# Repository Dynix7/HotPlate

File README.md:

# HotPlate
This is a design for an solder reflow hotplate controlled by an RP2040.

# Why I Made It
I made this PCB since I plan to solder more components in the future. But I currently only have an solder iron which is too big for smaller SMD components, so I can use this to easily solder those smaller components.

# Picture

|Name                      |Purpose                  |Quantity|Total Cost (USD)|Link                                                     |Distributor|
|--------------------------|-------------------------|--------|----------------|---------------------------------------------------------|-----------|
|70mm round Polymide Heater|Heating Element          |1       |3.92            |https://www.aliexpress.us/item/2255801077213882.html?mp=1|Aliexpress |
|PCB Stencil               |For Manual PCB Assembly  |1       |7.11            |                                                         |JLCPCB     |
|PCB                       |PCB for Build            |5       |5.10            |                                                         |JLCPCB     |
|100n Capacitor            |Capacitor                |100     |0.23            |https://www.lcsc.com/product-detail/C6119867.html        |LCSC       |
|1uF Capacitor             |Capacitor                |50      |0.27            |https://www.lcsc.com/product-detail/C59782.html          |LCSC       |
|10uF Capacitor            |Capacitor                |50      |0.40            |https://www.lcsc.com/product-detail/C19702.html          |LCSC       |
|12pF Capacitor            |Crystal Load Capacitors  |100     |0.28            |https://www.lcsc.com/product-detail/C45359931.html       |LCSC       |
|10k Resistor              |Resistor                 |100     |0.10            |https://www.lcsc.com/product-detail/C2930027.html        |LCSC       |
|1k Resistor               |Resistor                 |100     |0.09            |https://www.lcsc.com/product-detail/C2907113.html        |LCSC       |
|5.1k Resistor             |Resistor                 |100     |0.10            |https://www.lcsc.com/product-detail/C2907114.html        |LCSC       |
|27 Resistor               |Resistor                 |100     |0.10            |https://www.lcsc.com/product-detail/C2907021.html        |LCSC       |
|2.7k Resistor             |Resistor                 |100     |0.15            |https://www.lcsc.com/product-detail/C13167.html          |LCSC       |
|10 Resistor               |Resistor                 |20      |0.04            |https://www.lcsc.com/product-detail/C22859.html          |LCSC       |
|49.9 Resistor             |Resistor                 |100     |0.11            |https://www.lcsc.com/product-detail/C2930110.html        |LCSC       |
|22.6k Resistor            |REsistor                 |100     |0.12            |https://www.lcsc.com/product-detail/C2999509.html        |LCSC       |
|LED                       |Indicator LEDs           |50      |0.40            |https://www.lcsc.com/product-detail/C2827254.html        |LCSC       |
|100Ohm Resistor           |Resistor                 |100     |0.10            |https://www.lcsc.com/product-detail/C2906981.html        |LCSC       |
|Push Button               |Reset, Boot, Menu Buttons|20      |0.34            |https://www.lcsc.com/product-detail/C18078070.html       |LCSC       |
|SX3B12.000F1210F30 Crystal|Clock for RP2040         |5       |0.36            |https://www.lcsc.com/product-detail/C2901650.html        |LCSC       |
|LUTE 2920L500/30GR Fuse   |Prevents Overheating     |5       |0.74            |https://www.lcsc.com/product-detail/C19078763.html       |LCSC       |
|L78L33ACUTR               |Voltage Regulator        |5       |0.49            |https://www.lcsc.com/product-detail/C22358668.html       |LCSC       |
|USBLC6-2SC6               |Power Protection         |5       |0.77            |https://www.lcsc.com/product-detail/C7519.html           |LCSC       |
|RP2040                    |Microcontroller          |1       |0.95            |https://www.lcsc.com/product-detail/C2040.html           |LCSC       |
|HUSB238 USB PD Chip       | USB Power Delivery      |1       |0.50            |https://www.lcsc.com/product-detail/C7471904.html        |LCSC       |
|W25Q32JVSSIQ Flash Chip   |Storage of Program       |5       |7.51            |https://www.lcsc.com/product-detail/C179173.html         |LCSC       |
|N-Channel MOSFET          |Power Control            |5       |0.58            |https://www.lcsc.com/product-detail/C2902884.html        |LCSC       |
|P-Channel MOSFET          |Control Power            |1       |0.34            |https://www.lcsc.com/product-detail/C5277951.html        |LCSC       |
|2 Pin Terminal Block      |To Power Heating Element |5       |0.42            |https://www.lcsc.com/product-detail/C695629.html         |LCSC       |
|USB-C Receptacle          |Power                    |5       |0.41            |https://www.lcsc.com/product-detail/C2988369.html        |LCSC       |
|NTC Thermistor 100kΩ      |Thermometer              |5       |1.28            |https://www.lcsc.com/product-detail/C5355638.html        |LCSC       |

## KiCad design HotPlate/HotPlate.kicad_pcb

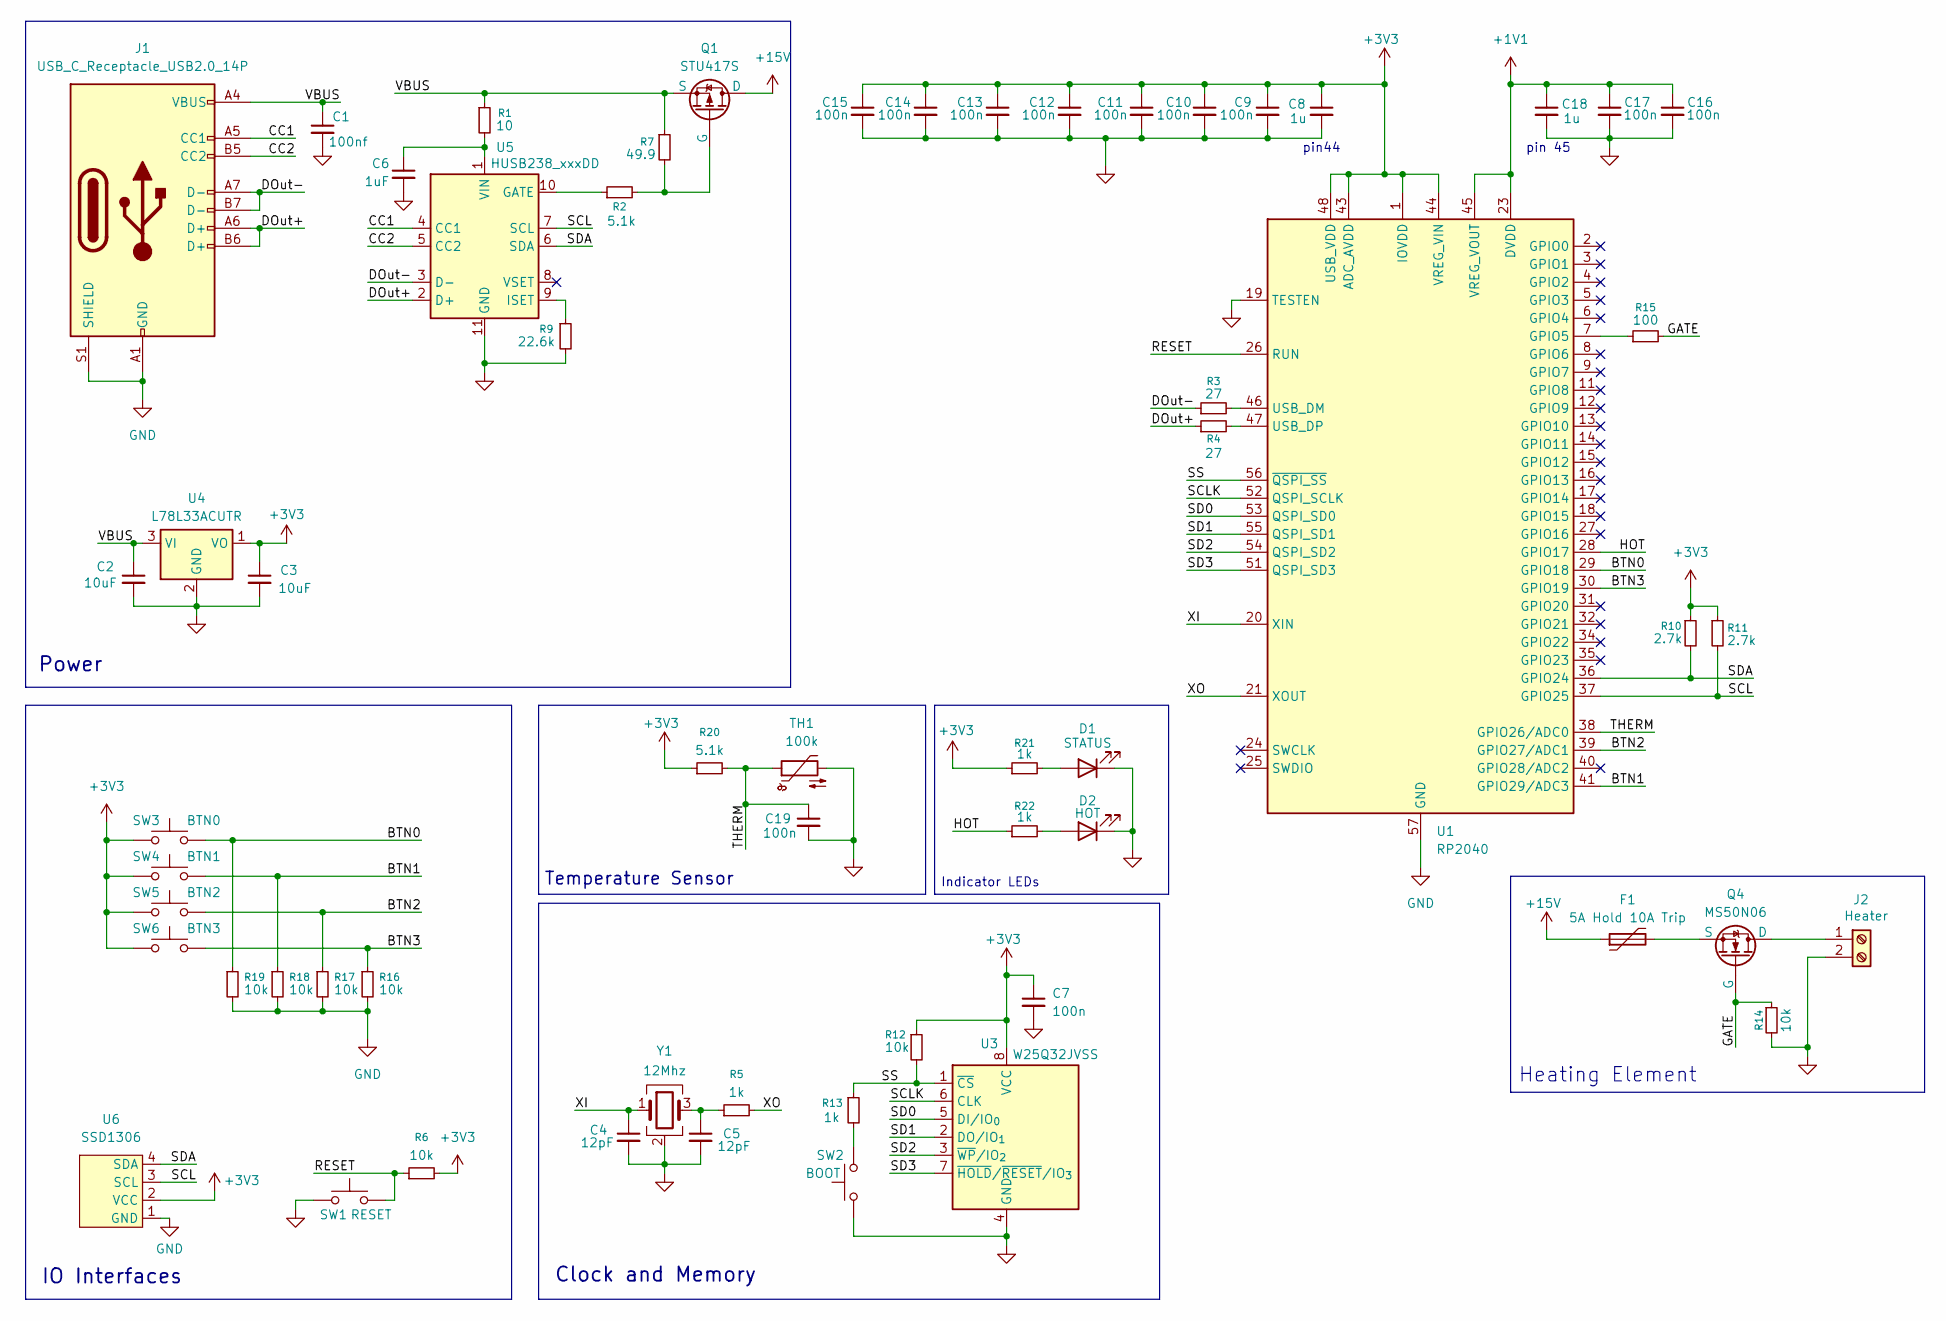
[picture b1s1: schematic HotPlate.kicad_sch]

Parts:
C1: 100nf; C_0603_1608Metric
C2, C3: 10uF; C_0603_1608Metric
C4, C5: 12pF; C_0603_1608Metric
C6: 1uF; C_0603_1608Metric
C7, C9, C10, C11, C12, C13, C14, C15, C16, C17, C19: 100n; C_0603_1608Metric
C8, C18: 1u; C_0603_1608Metric
D1: STATUS; D_1206_3216Metric
D2: HOT; D_1206_3216Metric
F1: 5A Hold 10A Trip; Fuse_2920_7451Metric
J1: USB_C_Receptacle_USB2.0_14P; USB_C_Receptacle_G-Switch_GT-USB-7010ASV
J2: Heater; TerminalBlock_Phoenix_PT-1,5-2-3.5-H_1x02_P3.50mm_Horizontal
Q1: STU417S; TO-252-2
Q4: MS50N06; TO-252-2
R1: 10; R_0603_1608Metric
R2, R20: 5.1k; R_0603_1608Metric
R3, R4: 27; R_0603_1608Metric
R5, R13, R21, R22: 1k; R_0603_1608Metric
R6, R12, R14, R16, R17, R18, R19: 10k; R_0603_1608Metric
R7: 49.9; R_0603_1608Metric
R9: 22.6k; R_0603_1608Metric
R10, R11: 2.7k; R_0603_1608Metric
R15: 100; R_0603_1608Metric
SW1: RESET; SW_SPST_PTS647_Sx38
SW2: BOOT; SW_SPST_PTS647_Sx38
SW3: BTN0; SW_SPST_PTS647_Sx38
SW4: BTN1; SW_SPST_PTS647_Sx38
SW5: BTN2; SW_SPST_PTS647_Sx38
SW6: BTN3; SW_SPST_PTS647_Sx38
TH1: 100k; R_Axial_DIN0204_L3.6mm_D1.6mm_P5.08mm_Horizontal
U1: RP2040; QFN-56-1EP_7x7mm_P0.4mm_EP3.2x3.2mm
U3: W25Q32JVSS; SOIC-8_5.3x5.3mm_P1.27mm
U4: L78L33ACUTR; SOT-89-3
U5: HUSB238_xxxDD; WDFN-10-1EP_3x3mm_P0.5mm_EP1.8x2.5mm
U6: SSD1306; PinHeader_1x04_P2.54mm_Vertical
Y1: 12Mhz; Oscillator_SMD_SeikoEpson_SG8002CE-4Pin_3.2x2.5mm

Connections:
+1V1: C16.1, C17.1, C18.1, U1.23 (DVDD), U1.45 (VREG_VOUT), U1.50 (DVDD)
+3V3: C3.1, C7.1, C8.1, C9.1, C10.1, C11.1, C12.1, C13.1, C14.1, C15.1, R6.2, R10.1, R11.1, R12.1, R20.1, R21.1, SW3.1, SW4.1, SW5.1, SW6.1, U1.1 (IOVDD), U1.10 (IOVDD), U1.22 (IOVDD), U1.33 (IOVDD), U1.42 (IOVDD), U1.43 (ADC_AVDD), U1.44 (VREG_VIN), U1.48 (USB_VDD), U1.49 (IOVDD), U3.8 (VCC), U4.1 (VO), U6.2 (VCC)
+15V: F1.1, Q1.2 (D)
/BTN0: R19.1, SW3.2, U1.29 (GPIO18)
/BTN1: R18.1, SW4.2, U1.41 (GPIO29/ADC3)
/BTN2: R17.1, SW5.2, U1.39 (GPIO27/ADC1)
/BTN3: R16.1, SW6.2, U1.30 (GPIO19)
/CC1: J1.A5 (CC1), U5.4 (CC1)
/CC2: J1.B5 (CC2), U5.5 (CC2)
/DOut+: J1.A6 (D+), J1.B6 (D+), R4.1, U5.2 (D+)
/DOut-: J1.A7 (D-), J1.B7 (D-), R3.1, U5.3 (D-)
/GATE: Q4.1 (G), R14.1, R15.2
/HOT: R22.1, U1.28 (GPIO17)
/RESET: R6.1, SW1.2, U1.26 (RUN)
/SCL: R11.2, U1.37 (GPIO25), U5.7 (SCL), U6.3 (SCL)
/SCLK: U1.52 (QSPI_SCLK), U3.6 (CLK)
/SD0: U1.53 (QSPI_SD0), U3.5 (DI/IO_{0})
/SD1: U1.55 (QSPI_SD1), U3.2 (DO/IO_{1})
/SD2: U1.54 (QSPI_SD2), U3.3 (~WP/IO_{2})
/SD3: U1.51 (QSPI_SD3), U3.7 (~HOLD/~RESET/IO_{3})
/SDA: R10.2, U1.36 (GPIO24), U5.6 (SDA), U6.4 (SDA)
/SS: R12.2, R13.1, U1.56 (~QSPI_SS), U3.1 (~CS)
/THERM: C19.1, R20.2, TH1.1, U1.38 (GPIO26/ADC0)
/VBUS: C1.1, C2.1, J1.A4 (VBUS), J1.A9 (VBUS), J1.B4 (VBUS), J1.B9 (VBUS), Q1.3 (S), R1.1, R7.1, U4.3 (VI)
/XI: C4.1, U1.20 (XIN), Y1.1
/XO: R5.2, U1.21 (XOUT)
GND: C1.2, C2.2, C3.2, C4.2, C5.2, C6.2, C7.2, C8.2, C9.2, C10.2, C11.2, C12.2, C13.2, C14.2, C15.2, C16.2, C17.2, C18.2, C19.2, D1.1 (K), D2.1 (K), J1.A1 (GND), J1.A12 (GND), J1.B1 (GND), J1.B12 (GND), J1.S1 (SHIELD), J2.2, R9.2, R14.2, R16.2, R17.2, R18.2, R19.2, SW1.1, SW2.1, TH1.2, U1.19 (TESTEN), U1.57 (GND), U3.4 (GND), U4.2 (GND), U5.11 (GND), U6.1 (GND), Y1.2 (G), Y1.4 (G)
unnamed: C5.1, R5.1, Y1.3
unnamed: D1.2 (A), R21.2
unnamed: D2.2 (A), R22.2
unnamed: J2.1, Q4.2 (D)
unnamed: Q1.1 (G), R2.2, R7.2
unnamed: F1.2, Q4.3 (S)
unnamed: R13.2, SW2.2
unnamed: R15.1, U1.7 (GPIO5)
unnamed: R3.2, U1.46 (USB_DM)
unnamed: R4.2, U1.47 (USB_DP)
unnamed: R2.1, U5.10 (GATE)
unnamed: R9.1, U5.9 (ISET)
unnamed: C6.1, R1.2, U5.1 (VIN)

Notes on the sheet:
Power
IO Interfaces
Heating Element
pin44
Temperature Sensor
Clock and Memory
Indicator LEDs
pin 45

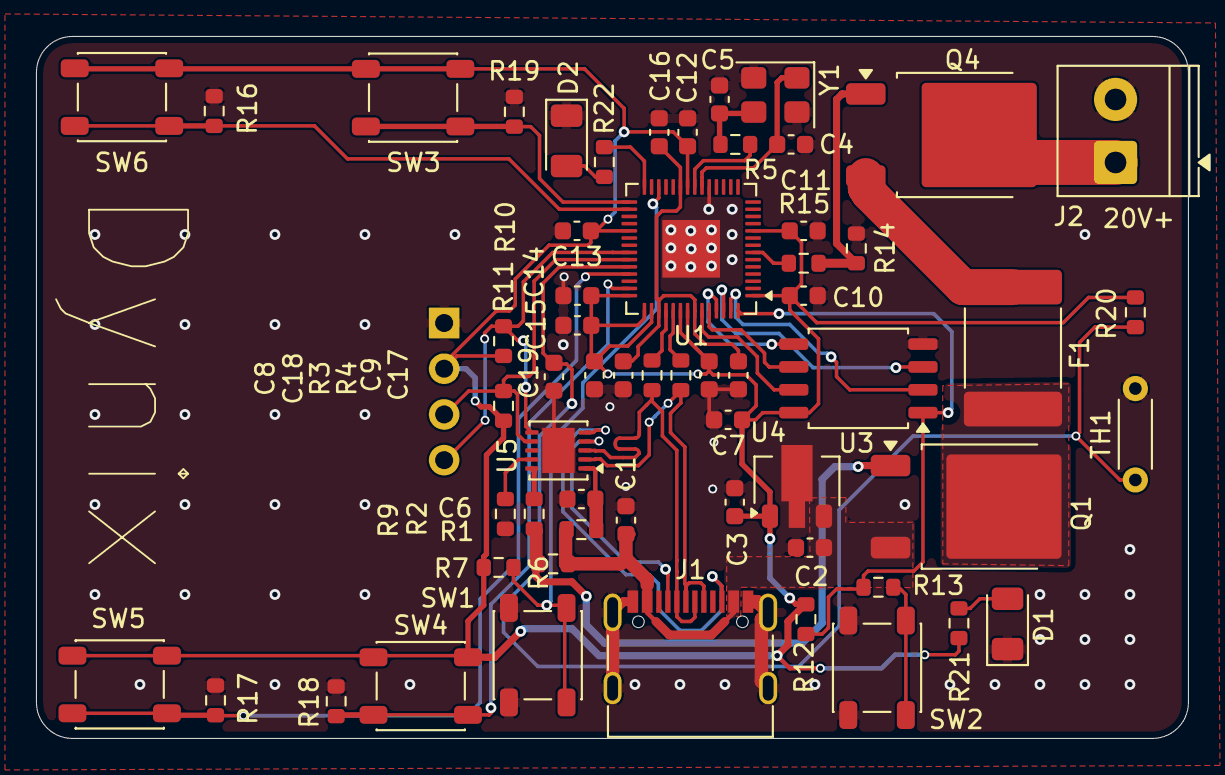
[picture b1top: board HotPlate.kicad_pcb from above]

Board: 2 copper layers, 64.0 x 39.0 mm, 60 parts (1 on the bottom side), 40 nets.

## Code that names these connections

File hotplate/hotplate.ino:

#include <Wire.h>
#include <Adafruit_SSD1306.h>
#include <Thermistor.h>
#include <NTC_Thermistor.h>

#include "thermistor.hpp"
#include "temperature.hpp"
#include "screen.hpp"
#include "helper.hpp"
#include "config.hpp"


NTC_Thermistor thermistor(THERM, REF_RESISTOR, NTC_RESISTANCE, NTC_REF_TEMP, B_VALUE, ANALOG_RES);
Adafruit_SSD1306 OLED_1306(SCREEN_WIDTH, SCREEN_HEIGHT, SCREEN_WIRE, OLED_RESET);

enum PLATESTATE currentState = STARTUP;

struct HEATINGPROFILE profile = {
    .targetTemps = {150.0, 220.0}, // Soak Temp, Reflow Temp-Celsius
    .targetTimes = {100, 60}, //Length of Soak, Length of Reflow-Seconds
    .targetRates = {2.5, 2.5, 3.5} // Start->Soak, Soak->Reflow, Reflow->End  -  Celsius/Second
}

HotPlateScreen SCREEN(&OLED_1306, &profile, &currentState);

void setup() {
    Serial.begin(115200);

    //I2C stuff
    Wire.begin();
    Wire.setSDA(SDA);
    Wire.setSCL(SCL);

    // Pinout Setup
    pinMode(BTN0, INPUT);
    pinMode(BTN1, INPUT);
    pinMode(BTN2, INPUT);
    pinMode(BTN3, INPUT);

    pinMode(GATE, OUTPUT);
    pinMode(HOT, OUTPUT); //LED

    pinMode(THERM, INPUT);

    SCREEN.initScreen();
}

void loop() {

  SCREEN.updateScreen();

}

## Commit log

2026-03-08 Initial USB and RP2040 Schematic
2026-03-09 Wire up power delivery, and memory
2026-03-10 Re-add buttons and add thermistor
2026-03-13 Wire Buttons, screen, thermistor, fuse
2026-03-14 Status LEDs
2026-03-15 Begin PCB placements and routing
2026-03-15 Finish routing
2026-03-19 Minor placement changes and ground vias
2026-03-21 Started Code and Added Name to PCB
2026-03-24 Minor code changes
2026-03-28 code for screen
2026-04-19 add ibom
2026-04-19 Change LED size
2026-04-19 Change button footprint
2026-04-20 udpate production
2026-05-09 Remove the USBLC6 since i forgot that im using 20v and not 5v
